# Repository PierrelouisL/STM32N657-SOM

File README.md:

The SOM is not finished yet, still in design.

Should be printed & assembled by November 2026.

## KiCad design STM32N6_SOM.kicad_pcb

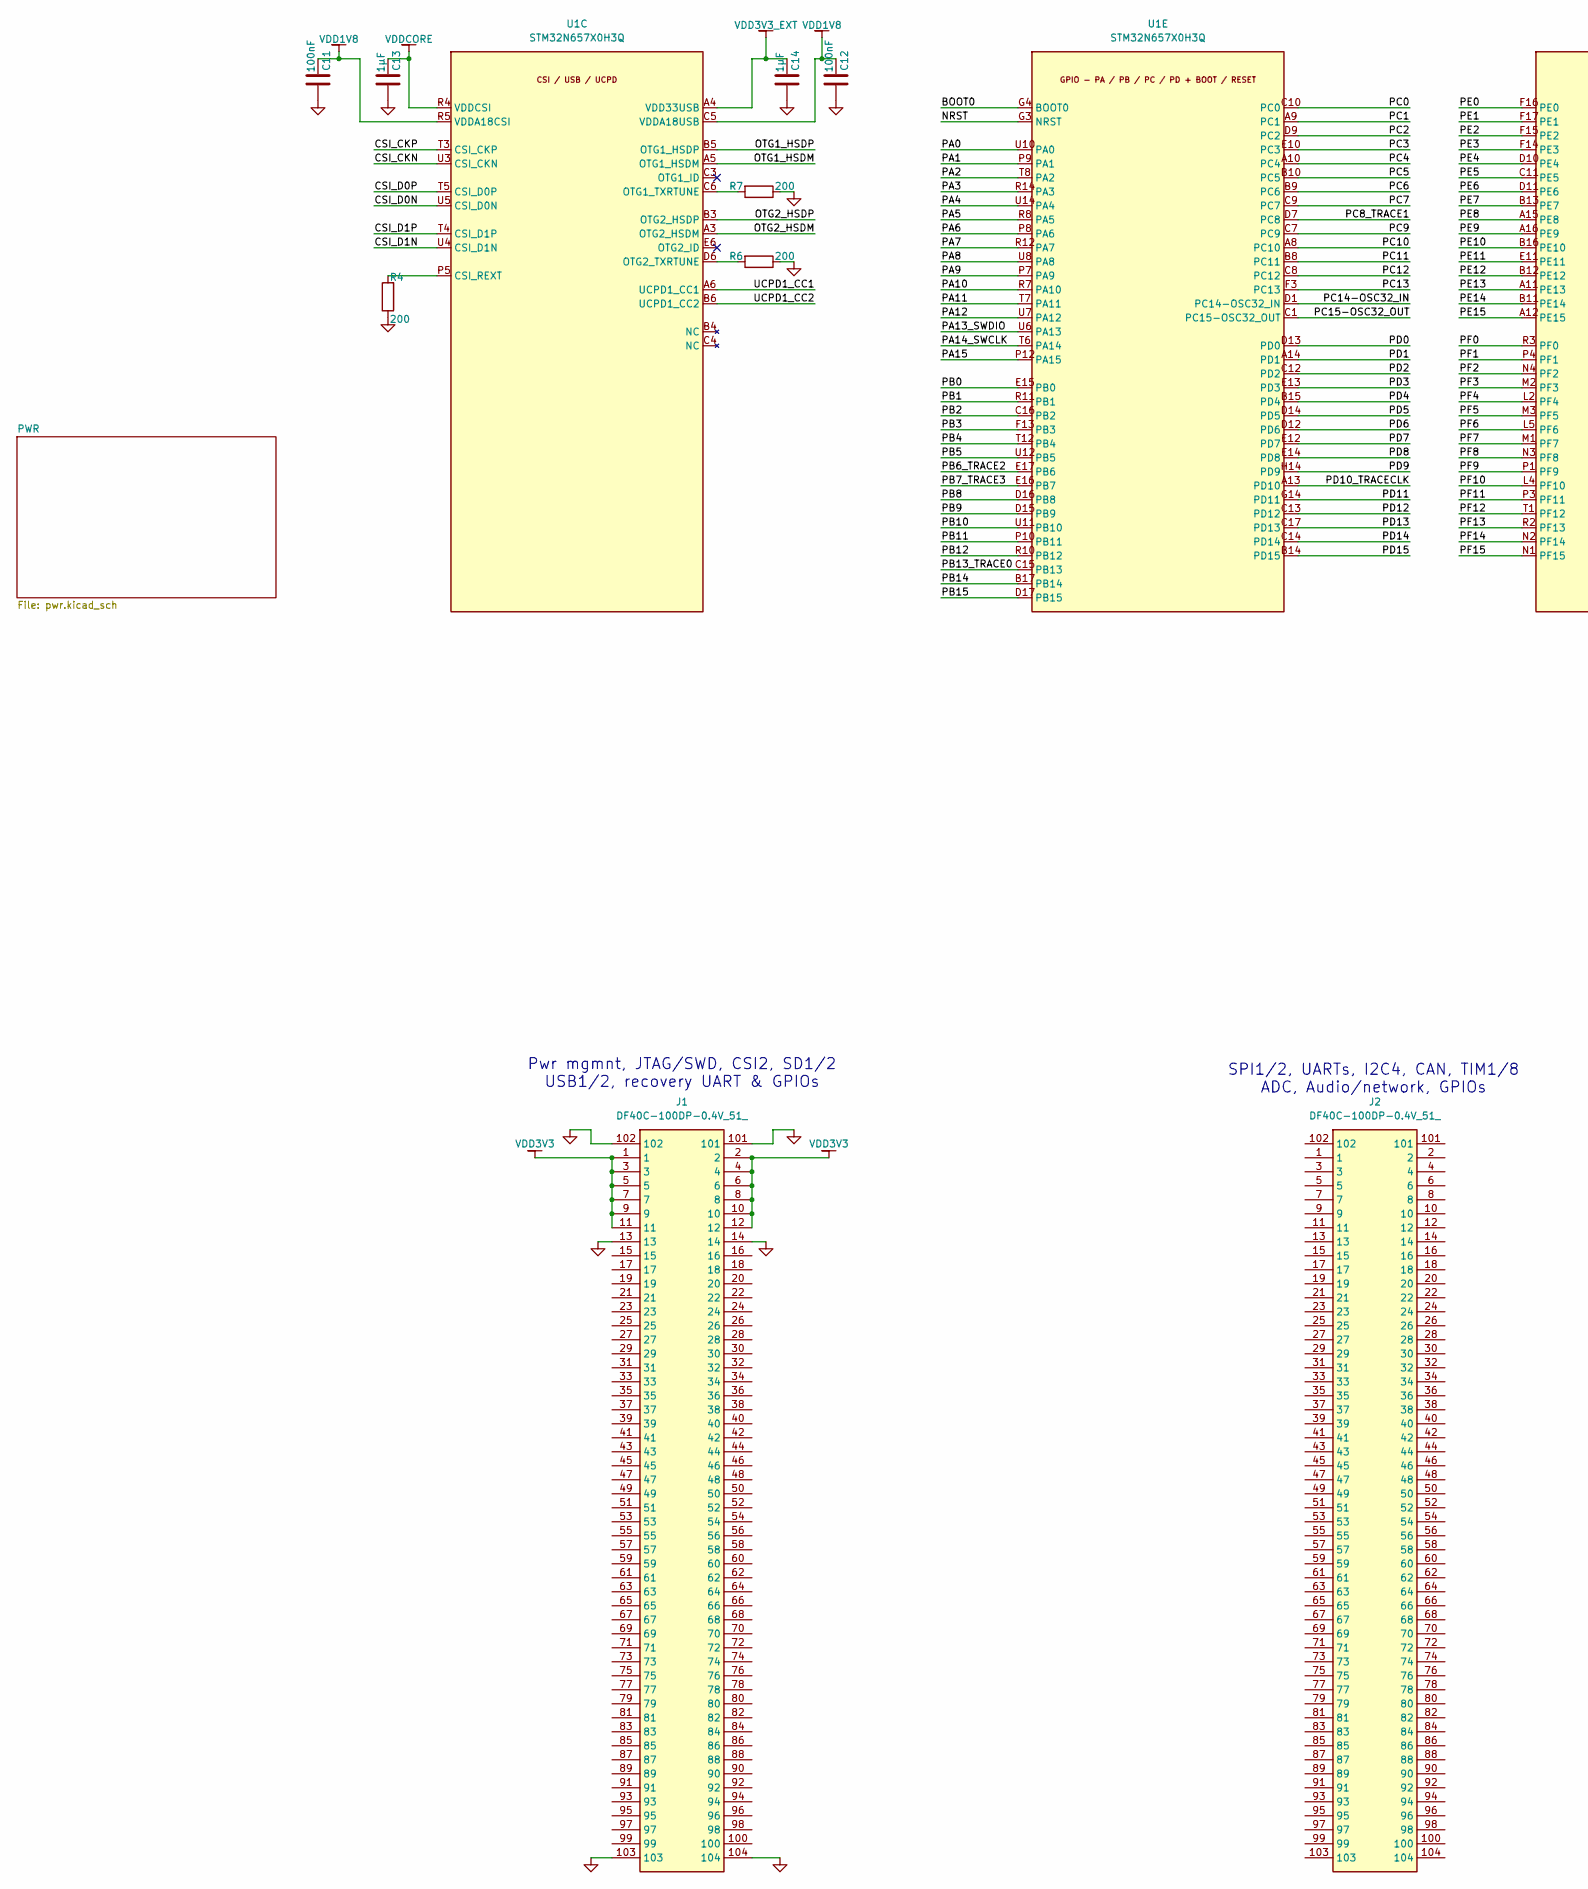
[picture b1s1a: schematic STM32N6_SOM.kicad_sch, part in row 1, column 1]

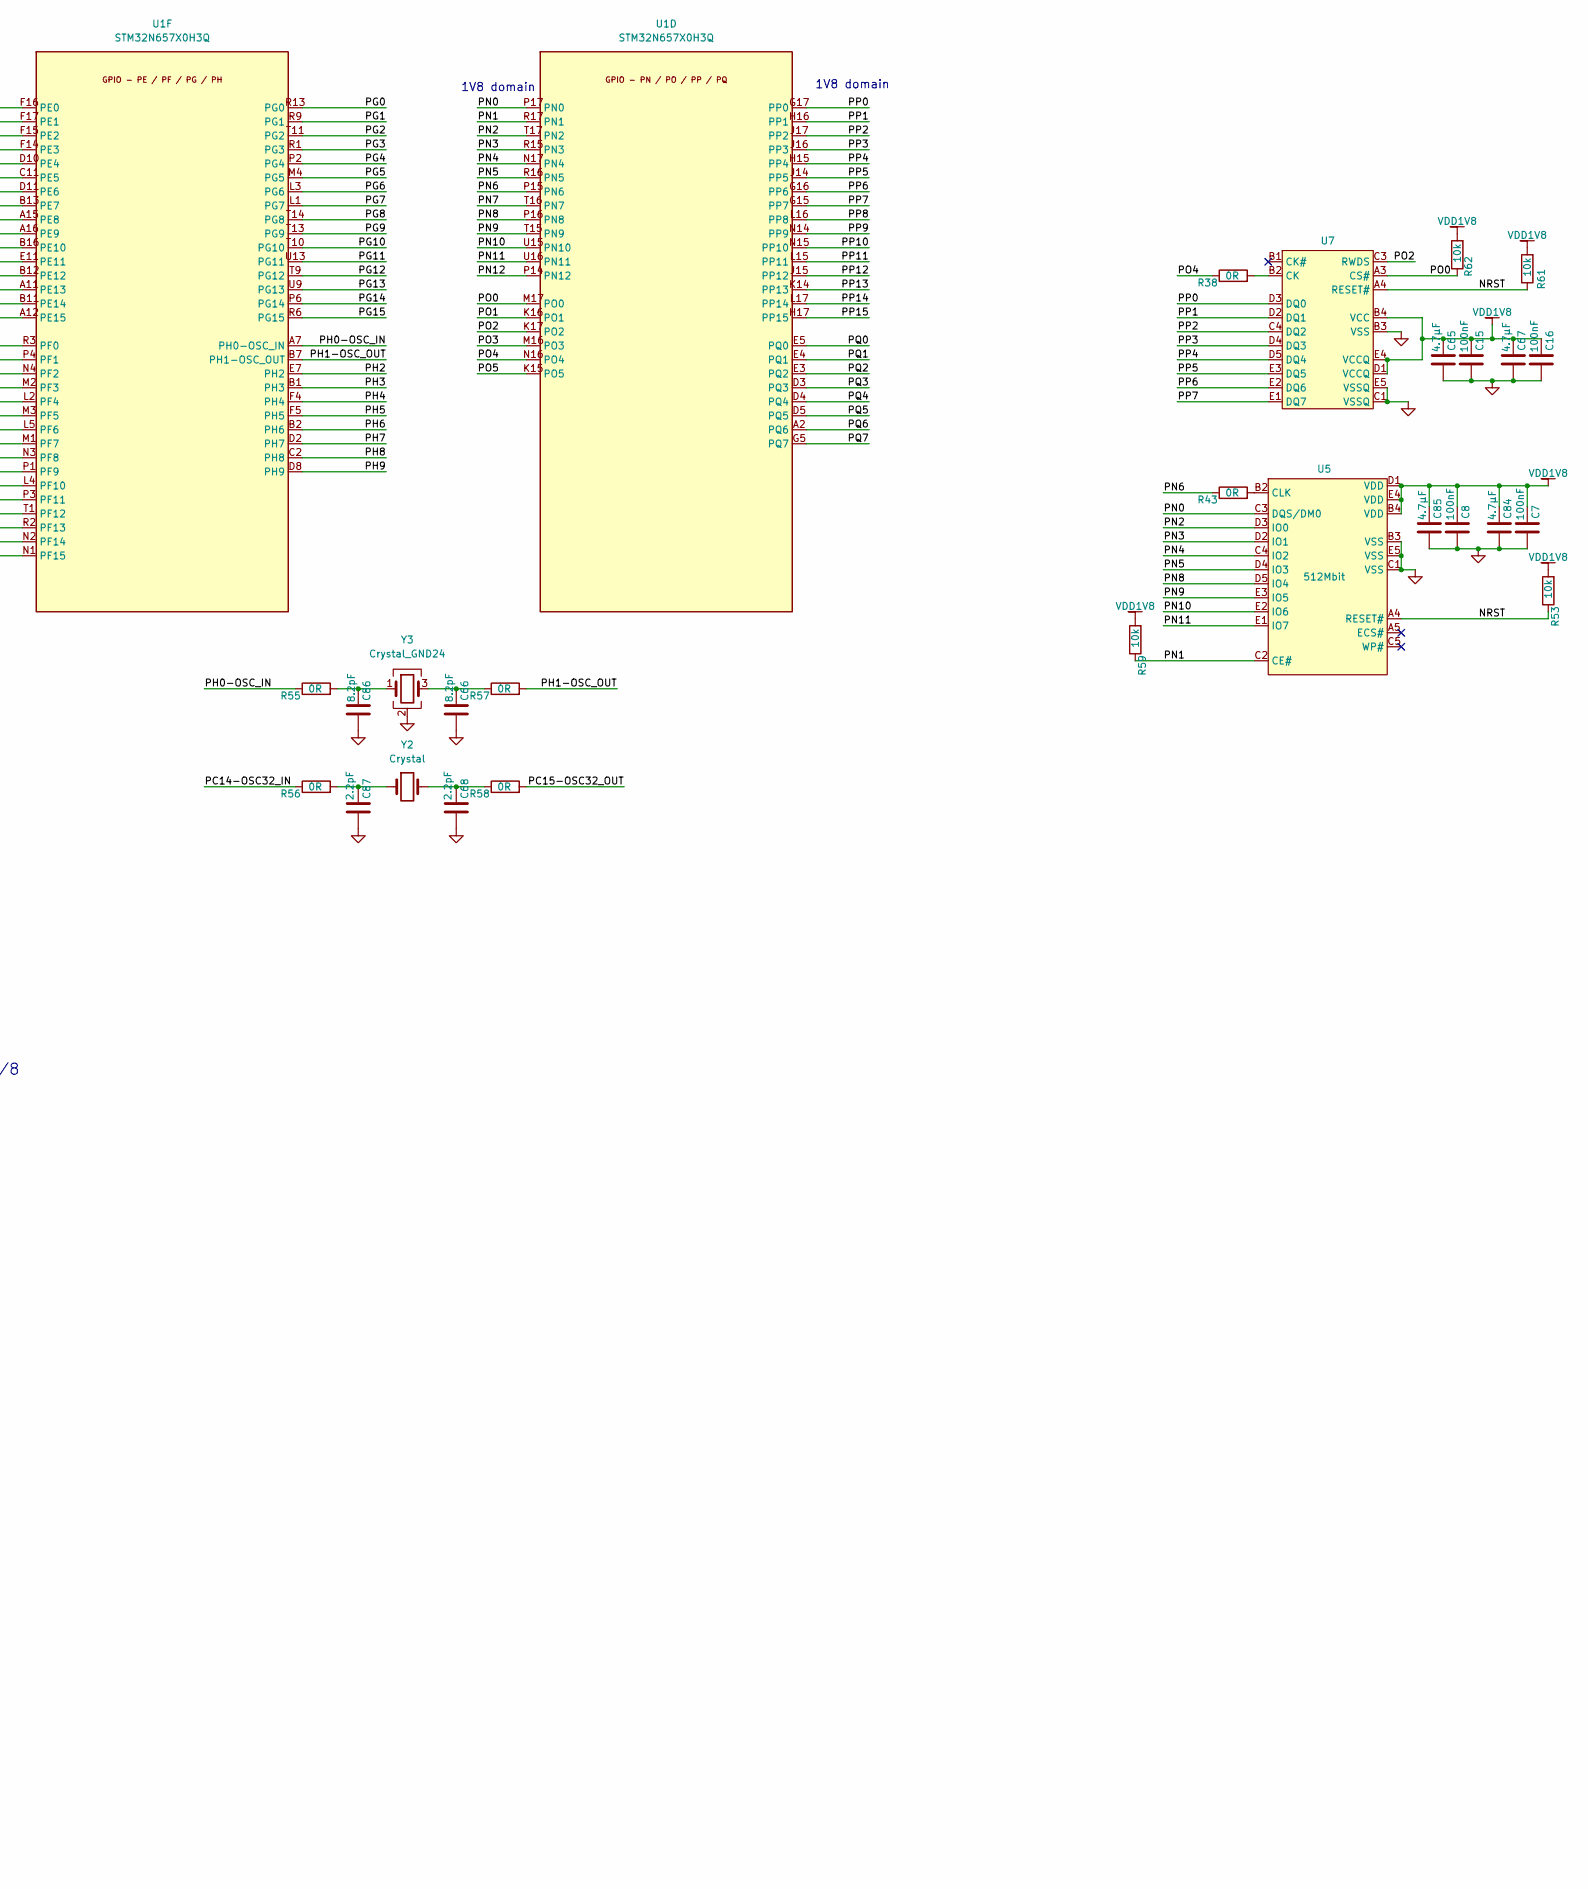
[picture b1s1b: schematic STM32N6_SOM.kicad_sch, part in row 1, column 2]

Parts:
C7, C8, C11, C12, C15, C16: 100nF; C_0201_0603Metric
C13, C14: 1µF; C_0201_0603Metric
C65, C67, C84, C85: 4.7µF; C_0402_1005Metric
C66, C86: 8.2pF; C_0402_1005Metric
C68, C87: 2.2pF; C_0402_1005Metric
J1, J2: DF40C-100DP-0.4V_51_; DF40C100DP04V51; Manufacturer_Part_Number DF40C-100DP-0.4V(51); Mouser Part Number 798-DF40C100DP0.4V51
R4, R6, R7: 200; R_0402_1005Metric
R38, R43, R55, R56, R57, R58: 0R; C_0402_1005Metric
R53, R59, R61, R62: 10k; C_0402_1005Metric
U1: STM32N657X0H3Q; BGA264C80P17X17_1400X1400X100; MPN STM32N657X0H3Q; LCSC Part C42418080
U5: 512Mbit; tfbga24 (6_8mm2); LCSC C20099949
U7: tfbga24 (6_8mm2); LCSC C7420405
Y2: Crystal; C1987116; LCSC C1987116
Y3: Crystal_GND24; C1985871; LCSC C1985871

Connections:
/BOOT0: U1.G4 (BOOT0)
/CSI_CKN: U1.U3 (CSI_CKN)
/CSI_CKP: U1.T3 (CSI_CKP)
/CSI_D0N: U1.U5 (CSI_D0N)
/CSI_D0P: U1.T5 (CSI_D0P)
/CSI_D1N: U1.U4 (CSI_D1N)
/CSI_D1P: U1.T4 (CSI_D1P)
/NRST: R53.1, R61.1, U1.G3 (NRST), U5.A4 (RESET#), U7.A4 (RESET#)
/OTG1_HSDM: U1.A5 (OTG1_HSDM)
/OTG1_HSDP: U1.B5 (OTG1_HSDP)
/OTG2_HSDM: U1.A3 (OTG2_HSDM)
/OTG2_HSDP: U1.B3 (OTG2_HSDP)
/PA0: U1.U10 (PA0)
/PA1: U1.P9 (PA1)
/PA2: U1.T8 (PA2)
/PA3: U1.R14 (PA3)
/PA4: U1.U14 (PA4)
/PA5: U1.R8 (PA5)
/PA6: U1.P8 (PA6)
/PA7: U1.R12 (PA7)
/PA8: U1.U8 (PA8)
/PA9: U1.P7 (PA9)
/PA10: U1.R7 (PA10)
/PA11: U1.T7 (PA11)
/PA12: U1.U7 (PA12)
/PA13_SWDIO: U1.U6 (PA13)
/PA14_SWCLK: U1.T6 (PA14)
/PA15: U1.P12 (PA15)
/PB0: U1.E15 (PB0)
/PB1: U1.R11 (PB1)
/PB2: U1.C16 (PB2)
/PB3: U1.F13 (PB3)
/PB4: U1.T12 (PB4)
/PB5: U1.U12 (PB5)
/PB6_TRACE2: U1.E17 (PB6)
/PB7_TRACE3: U1.E16 (PB7)
/PB8: U1.D16 (PB8)
/PB9: U1.D15 (PB9)
/PB10: U1.U11 (PB10)
/PB11: U1.P10 (PB11)
/PB12: U1.R10 (PB12)
/PB13_TRACE0: U1.C15 (PB13)
/PB14: U1.B17 (PB14)
/PB15: U1.D17 (PB15)
/PC0: U1.C10 (PC0)
/PC1: U1.A9 (PC1)
/PC2: U1.D9 (PC2)
/PC3: U1.E10 (PC3)
/PC4: U1.A10 (PC4)
/PC5: U1.B10 (PC5)
/PC6: U1.B9 (PC6)
/PC7: U1.C9 (PC7)
/PC8_TRACE1: U1.D7 (PC8)
/PC9: U1.C7 (PC9)
/PC10: U1.A8 (PC10)
/PC11: U1.B8 (PC11)
/PC12: U1.C8 (PC12)
/PC13: U1.F3 (PC13)
/PC14-OSC32_IN: R56.1, U1.D1 (PC14-OSC32_IN)
/PC15-OSC32_OUT: R58.2, U1.C1 (PC15-OSC32_OUT)
/PD0: U1.D13 (PD0)
/PD1: U1.A14 (PD1)
/PD2: U1.C12 (PD2)
/PD3: U1.E13 (PD3)
/PD4: U1.B15 (PD4)
/PD5: U1.D14 (PD5)
/PD6: U1.D12 (PD6)
/PD7: U1.E12 (PD7)
/PD8: U1.E14 (PD8)
/PD9: U1.H14 (PD9)
/PD10_TRACECLK: U1.A13 (PD10)
/PD11: U1.G14 (PD11)
/PD12: U1.C13 (PD12)
/PD13: U1.C17 (PD13)
/PD14: U1.C14 (PD14)
/PD15: U1.B14 (PD15)
/PE0: U1.F16 (PE0)
/PE1: U1.F17 (PE1)
/PE2: U1.F15 (PE2)
/PE3: U1.F14 (PE3)
/PE4: U1.D10 (PE4)
/PE5: U1.C11 (PE5)
/PE6: U1.D11 (PE6)
/PE7: U1.B13 (PE7)
/PE8: U1.A15 (PE8)
/PE9: U1.A16 (PE9)
/PE10: U1.B16 (PE10)
/PE11: U1.E11
/PE12: U1.B12 (PE12)
/PE13: U1.A11 (PE13)
/PE14: U1.B11 (PE14)
/PE15: U1.A12 (PE15)
/PF0: U1.R3 (PF0)
/PF1: U1.P4 (PF1)
/PF2: U1.N4 (PF2)
/PF3: U1.M2 (PF3)
/PF4: U1.L2 (PF4)
/PF5: U1.M3 (PF5)
/PF6: U1.L5 (PF6)
/PF7: U1.M1 (PF7)
/PF8: U1.N3 (PF8)
/PF9: U1.P1 (PF9)
/PF10: U1.L4 (PF10)
/PF11: U1.P3 (PF11)
/PF12: U1.T1 (PF12)
/PF13: U1.R2 (PF13)
/PF14: U1.N2 (PF14)
/PF15: U1.N1 (PF15)
/PG0: U1.R13 (PG0)
/PG1: U1.R9 (PG1)
/PG2: U1.T11 (PG2)
/PG3: U1.R1 (PG3)
/PG4: U1.P2 (PG4)
/PG5: U1.M4 (PG5)
/PG6: U1.L3 (PG6)
/PG7: U1.L1 (PG7)
/PG8: U1.T14 (PG8)
/PG9: U1.T13 (PG9)
/PG10: U1.T10 (PG10)
/PG11: U1.U13 (PG11)
/PG12: U1.T9 (PG12)
/PG13: U1.U9 (PG13)
/PG14: U1.P6 (PG14)
/PG15: U1.R6 (PG15)
/PH0-OSC_IN: R55.1, U1.A7 (PH0-OSC_IN)
/PH1-OSC_OUT: R57.2, U1.B7 (PH1-OSC_OUT)
/PH2: U1.E7 (PH2)
/PH3: U1.B1 (PH3)
/PH4: U1.F4 (PH4)
/PH5: U1.F5 (PH5)
/PH6: U1.B2 (PH6)
/PH7: U1.D2 (PH7)
/PH8: U1.C2 (PH8)
/PH9: U1.D8 (PH9)
/PN0: U1.P17 (PN0), U5.C3 (DQS/DM0)
/PN1: R59.1, U1.R17 (PN1), U5.C2 (CE#)
/PN2: U1.T17 (PN2), U5.D3 (IO0)
/PN3: U1.R15 (PN3), U5.D2 (IO1)
/PN4: U1.N17 (PN4), U5.C4 (IO2)
/PN5: U1.R16 (PN5), U5.D4 (IO3)
/PN6: R43.1, U1.P15 (PN6)
/PN7: U1.T16 (PN7)
/PN8: U1.P16 (PN8), U5.D5 (IO4)
/PN9: U1.T15 (PN9), U5.E3 (IO5)
/PN10: U1.U15 (PN10), U5.E2 (IO6)
/PN11: U1.U16 (PN11), U5.E1 (IO7)
/PN12: U1.P14 (PN12)
/PO0: R62.1, U1.M17 (PO0), U7.A3 (CS#)
/PO1: U1.K16 (PO1)
/PO2: U1.K17 (PO2), U7.C3 (RWDS)
/PO3: U1.M16 (PO3)
/PO4: R38.1, U1.N16 (PO4)
/PO5: U1.K15 (PO5)
/PP0: U1.G17 (PP0), U7.D3 (DQ0)
/PP1: U1.H16 (PP1), U7.D2 (DQ1)
/PP2: U1.J17 (PP2), U7.C4 (DQ2)
/PP3: U1.J16 (PP3), U7.D4 (DQ3)
/PP4: U1.H15 (PP4), U7.D5 (DQ4)
/PP5: U1.J14 (PP5), U7.E3 (DQ5)
/PP6: U1.G16 (PP6), U7.E2 (DQ6)
/PP7: U1.G15 (PP7), U7.E1 (DQ7)
/PP8: U1.L16 (PP8)
/PP9: U1.N14 (PP9)
/PP10: U1.N15 (PP10)
/PP11: U1.L15 (PP11)
/PP12: U1.J15 (PP12)
/PP13: U1.K14 (PP13)
/PP14: U1.L17 (PP14)
/PP15: U1.H17 (PP15)
/PQ0: U1.E5 (PQ0)
/PQ1: U1.E4 (PQ1)
/PQ2: U1.E3 (PQ2)
/PQ3: U1.D3 (PQ3)
/PQ4: U1.D4 (PQ4)
/PQ5: U1.D5 (PQ5)
/PQ6: U1.A2 (PQ6)
/PQ7: U1.G5 (PQ7)
/UCPD1_CC1: U1.A6 (UCPD1_CC1)
/UCPD1_CC2: U1.B6 (UCPD1_CC2)
GND: C7.2, C8.2, C11.2, C12.2, C13.2, C14.2, C15.2, C16.2, C65.2, C66.2, C67.2, C68.2, C84.2, C85.2, C86.2, C87.2, J1.13, J1.14, J1.101, J1.102, J1.103, J1.104, R4.1, R6.1, R7.1, U5.B3 (VSS), U5.C1 (VSS), U5.E5 (VSS), U7.B3 (VSS), U7.C1 (VSSQ), U7.E5 (VSSQ), Y3.2 (G), Y3.4 (G); also elsewhere on the board
unnamed: C66.1, R57.1, Y3.3
unnamed: C68.1, R58.1, Y2.2
unnamed: C86.1, R55.2, Y3.1
unnamed: C87.1, R56.2, Y2.1
unnamed: R4.2, U1.P5 (CSI_REXT)
unnamed: R7.2, U1.C6 (OTG1_TXRTUNE)
unnamed: R6.2, U1.D6 (OTG2_TXRTUNE)
unnamed: R43.2, U5.B2 (CLK)
unnamed: U5.A2 (NC), U5.A3 (NC), U5.B1 (NC), U5.B5 (NC)
unnamed: R38.2, U7.B2 (CK)
VDD1V8: C7.1, C8.1, C11.1, C12.1, C15.1, C16.1, C65.1, C67.1, C84.1, C85.1, R53.2, R59.2, R61.2, R62.2, U1.C5 (VDDA18USB), U1.R5 (VDDA18CSI), U5.B4 (VDD), U5.D1 (VDD), U5.E4 (VDD), U7.B4 (VCC), U7.D1 (VCCQ), U7.E4 (VCCQ); also elsewhere on the board
VDD3V3: J1.1, J1.2, J1.3, J1.4, J1.5, J1.6, J1.7, J1.8, J1.9, J1.10, J1.11, J1.12; also elsewhere on the board
VDD3V3_EXT: C14.1, U1.A4 (VDD33USB); also elsewhere on the board
VDDCORE: C13.1, U1.R4 (VDDCSI); also elsewhere on the board

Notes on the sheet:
1V8 domain
Pwr mgmnt, JTAG/SWD, CSI2, SD1/2 USB1/2, recovery UART & GPIOs
SPI1/2, UARTs, I2C4, CAN, TIM1/8 ADC, Audio/network, GPIOs

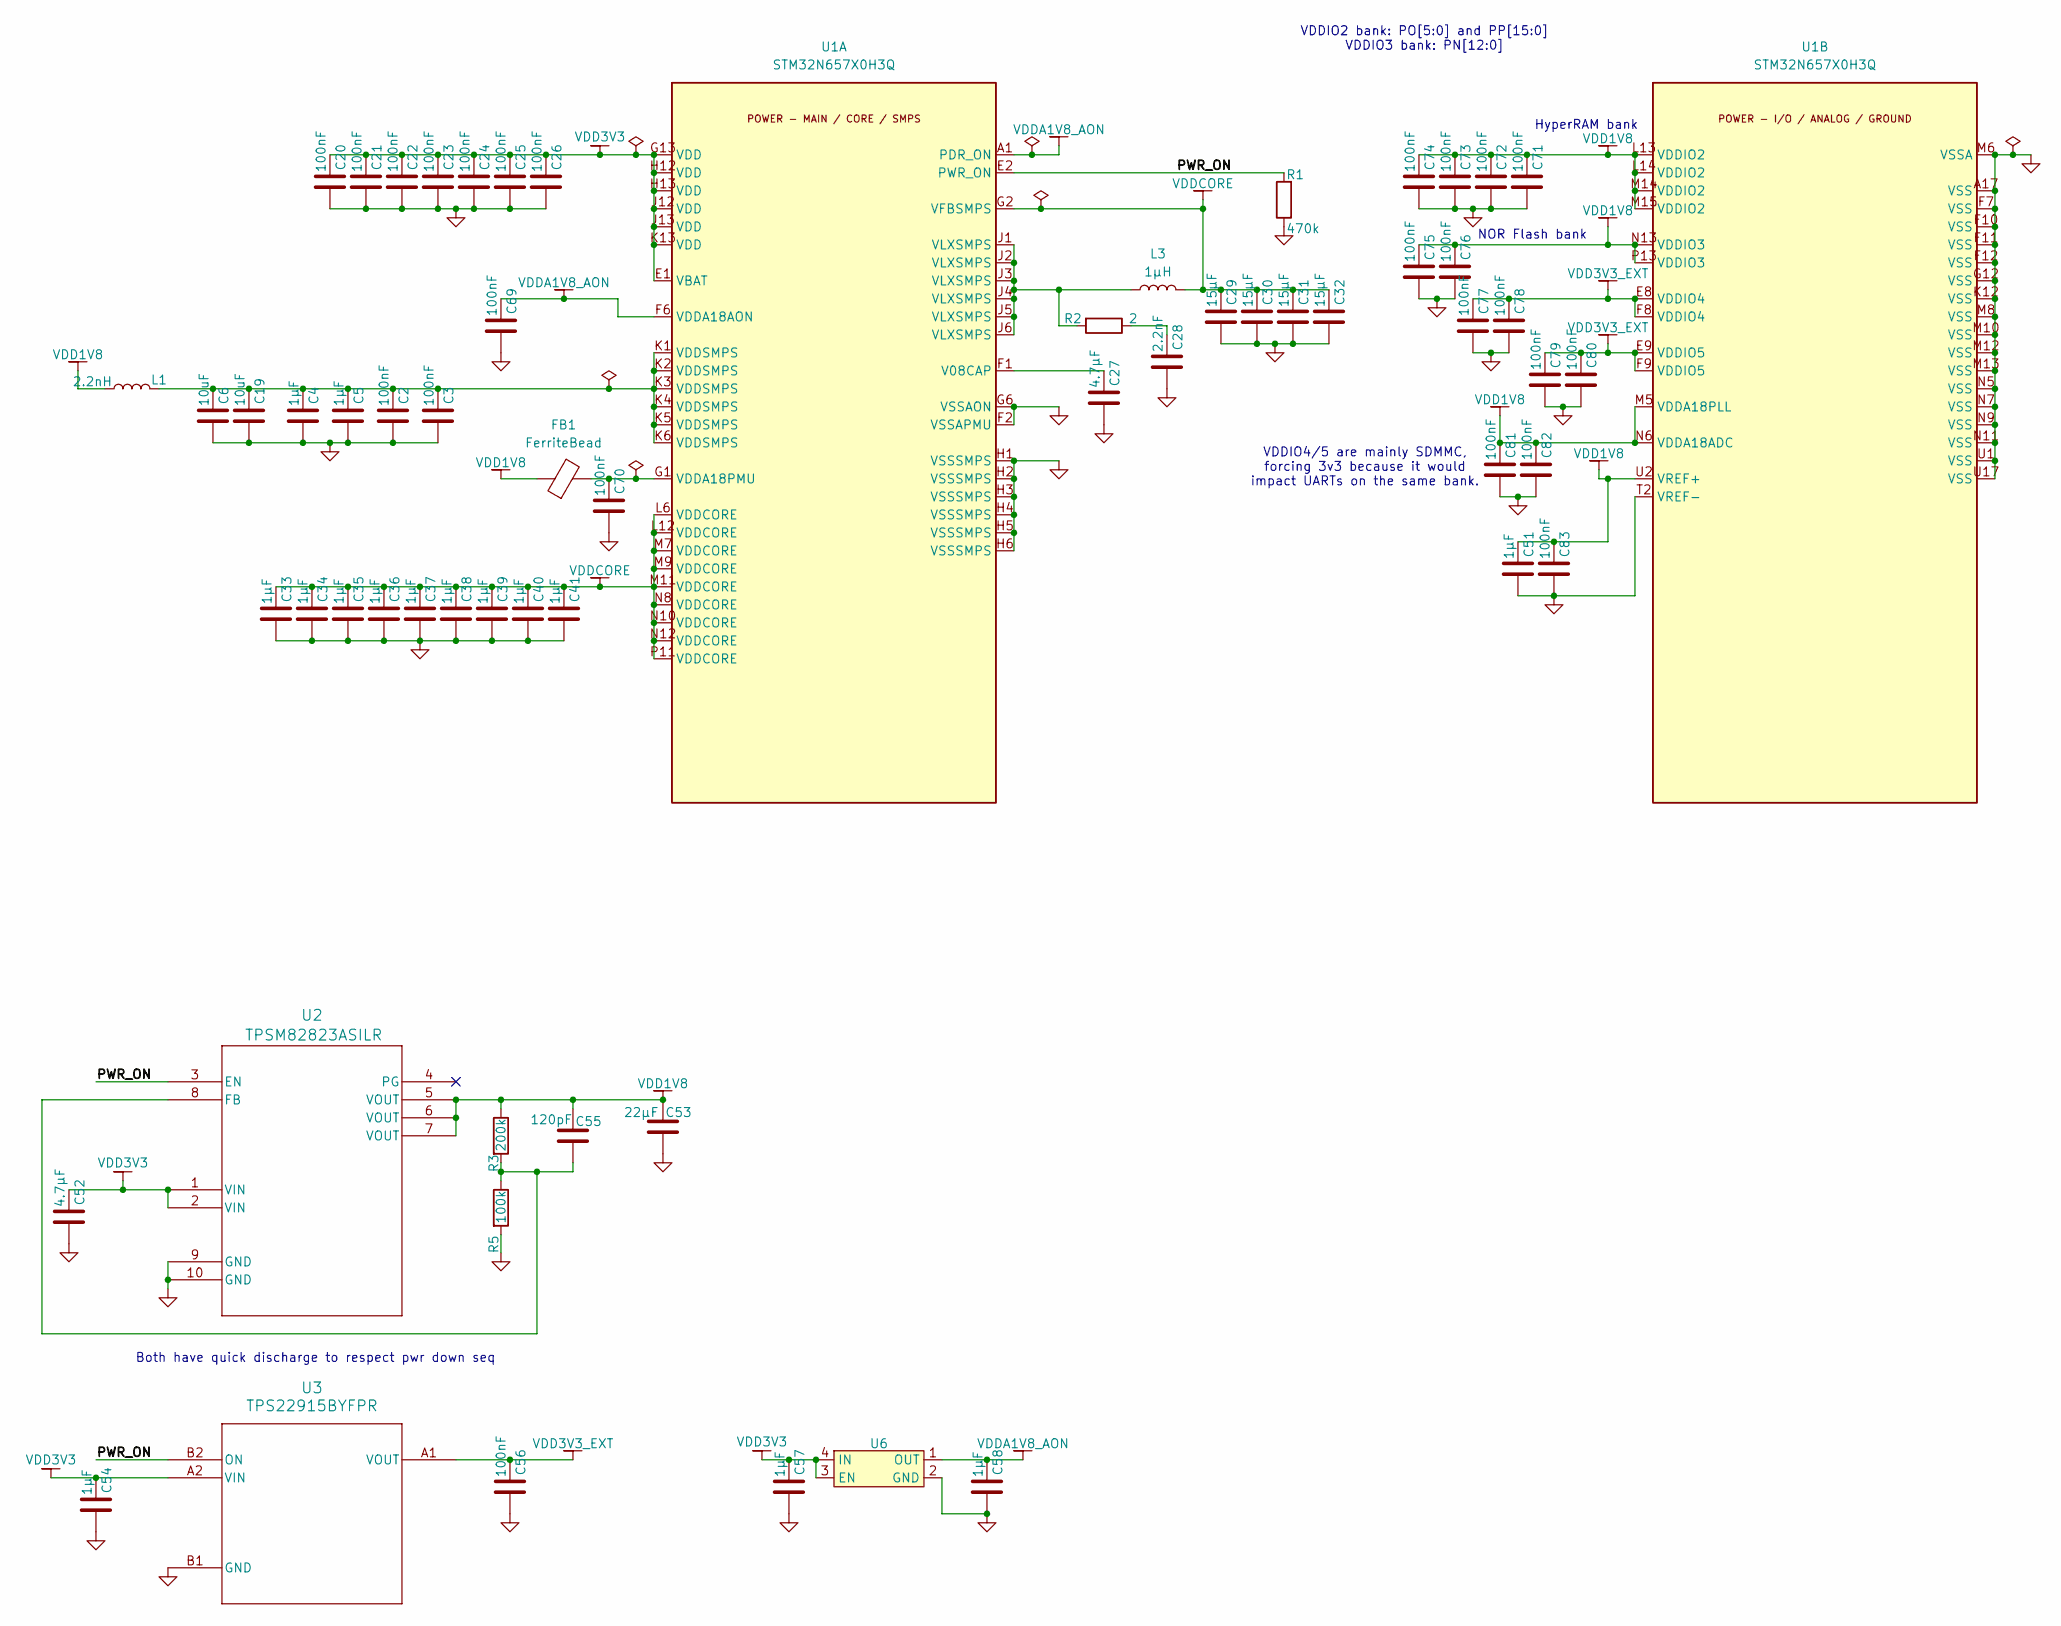
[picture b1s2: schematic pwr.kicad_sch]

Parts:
C2, C3, C20, C21, C22, C23, C24, C25, C26, C69, C70, C71, C72, C73, C74, C75, C76, C77, C78, C79, C80, C81, C82, C83: 100nF; C_0201_0603Metric
C4, C5, C33, C34, C35, C36, C37, C38, C39, C40, C41, C51: 1µF; C_0201_0603Metric
C6, C19: 10uF; C_0402_1005Metric
C27: 4.7µF; C_0402_1005Metric
C28: 2.2nF; C_0402_1005Metric
C29, C30, C31, C32: 15µF; C_0603_1608Metric
C52: 4.7µF; C_0603_1608Metric
C53: 22µF; C_0603_1608Metric
C54, C57, C58: 1µF; C_0402_1005Metric
C55: 120pF; C_0603_1608Metric
C56: 100nF; C_0402_1005Metric
FB1: FerriteBead; L_0201_0603Metric; LCSC C3032750
L1: 2.2nH; C_0603_1608Metric
L3: 1µH; C_0805_2012Metric; LCSC C1042
R1: 470k; R_0402_1005Metric; LCSC C25790
R2: 2; R_0402_1005Metric
R3: 200k; R_0402_1005Metric
R5: 100k; R_0402_1005Metric
U1: STM32N657X0H3Q; BGA264C80P17X17_1400X1400X100; MPN STM32N657X0H3Q; LCSC Part C42418080
U2: TPSM82823ASILR; SIL0010D_TEX; LCSC C5219332
U3: TPS22915BYFPR; YFP4_TEX; LCSC C478464
U6: DQN_X2SON4_1mmx1mm; LCSC C3744287

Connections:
/PWR/PWR_ON: R1.2, U1.E2 (PWR_ON), U2.3 (EN), U3.B2 (ON)
GND: C2.2, C3.2, C4.2, C5.2, C6.2, C19.2, C20.2, C21.2, C22.2, C23.2, C24.2, C25.2, C26.2, C27.2, C28.2, C29.2, C30.2, C31.2, C32.2, C33.2, C34.2, C35.2, C36.2, C37.2, C38.2, C39.2, C40.2, C41.2, C51.2, C52.2, C53.2, C54.2, C56.2, C57.2, C58.2, C69.2, C70.2, C71.2, C72.2, C73.2, C74.2, C75.2, C76.2, C77.2, C78.2, C79.2, C80.2, C81.2, C82.2, C83.2, R1.1, R5.2, U1.A17 (VSS), U1.F2 (VSSAPMU), U1.F7 (VSS), U1.F10 (VSS), U1.F11 (VSS), U1.F12 (VSS), U1.G6 (VSSAON), U1.G12 (VSS), U1.H1 (VSSSMPS), U1.H2 (VSSSMPS), U1.H3 (VSSSMPS), U1.H4 (VSSSMPS), U1.H5 (VSSSMPS), U1.H6 (VSSSMPS), U1.K12 (VSS), U1.M6 (VSSA), U1.M8 (VSS), U1.M10 (VSS), U1.M12 (VSS), U1.M13 (VSS), U1.N5 (VSS), U1.N7 (VSS), U1.N9 (VSS), U1.N11 (VSS), U1.T2 (VREF-), U1.U1 (VSS), U1.U17 (VSS), U2.9 (GND), U2.10 (GND), U3.B1 (GND), U6.2 (GND), U6.5 (THERM); also elsewhere on the board
unnamed: C2.1, C3.1, C4.1, C5.1, C6.1, C19.1, L1.1, U1.K1 (VDDSMPS), U1.K2 (VDDSMPS), U1.K3 (VDDSMPS), U1.K4 (VDDSMPS), U1.K5 (VDDSMPS), U1.K6 (VDDSMPS)
unnamed: C28.1, R2.1
unnamed: L3.2, R2.2, U1.J1 (VLXSMPS), U1.J2 (VLXSMPS), U1.J3 (VLXSMPS), U1.J4 (VLXSMPS), U1.J5 (VLXSMPS), U1.J6 (VLXSMPS)
unnamed: C27.1, U1.F1 (V08CAP)
unnamed: C70.1, FB1.2, U1.G1 (VDDA18PMU)
unnamed: C55.2, R3.2, R5.1, U2.8 (FB)
VDD1V8: C51.1, C53.1, C55.1, C71.1, C72.1, C73.1, C74.1, C75.1, C76.1, C81.1, C82.1, C83.1, FB1.1, L1.2, R3.1, U1.L13 (VDDIO2), U1.L14 (VDDIO2), U1.M5 (VDDA18PLL), U1.M14 (VDDIO2), U1.M15 (VDDIO2), U1.N6 (VDDA18ADC), U1.N13 (VDDIO3), U1.P13 (VDDIO3), U1.U2 (VREF+), U2.5 (VOUT), U2.6 (VOUT), U2.7 (VOUT); also elsewhere on the board
VDD3V3: C20.1, C21.1, C22.1, C23.1, C24.1, C25.1, C26.1, C52.1, C54.1, C57.1, U1.E1 (VBAT), U1.G13 (VDD), U1.H12 (VDD), U1.H13 (VDD), U1.J12 (VDD), U1.J13 (VDD), U1.K13 (VDD), U2.1 (VIN), U2.2 (VIN), U3.A2 (VIN), U6.3 (EN), U6.4 (IN); also elsewhere on the board
VDD3V3_EXT: C56.1, C77.1, C78.1, C79.1, C80.1, U1.E8 (VDDIO4), U1.E9 (VDDIO5), U1.F8 (VDDIO4), U1.F9 (VDDIO5), U3.A1 (VOUT); also elsewhere on the board
VDDA1V8_AON: C58.1, C69.1, U1.A1 (PDR_ON), U1.F6 (VDDA18AON), U6.1 (OUT)
VDDCORE: C29.1, C30.1, C31.1, C32.1, C33.1, C34.1, C35.1, C36.1, C37.1, C38.1, C39.1, C40.1, C41.1, L3.1, U1.G2 (VFBSMPS), U1.L6 (VDDCORE), U1.L12 (VDDCORE), U1.M7 (VDDCORE), U1.M9 (VDDCORE), U1.M11 (VDDCORE), U1.N8 (VDDCORE), U1.N10 (VDDCORE), U1.N12 (VDDCORE), U1.P11 (VDDCORE); also elsewhere on the board

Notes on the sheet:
VDDIO2 bank: PO[5:0] and PP[15:0] VDDIO3 bank: PN[12:0]
Both have quick discharge to respect pwr down seq
VDDIO4/5 are mainly SDMMC, forcing 3v3 because it would impact UARTs on the same bank.
HyperRAM bank
NOR Flash bank

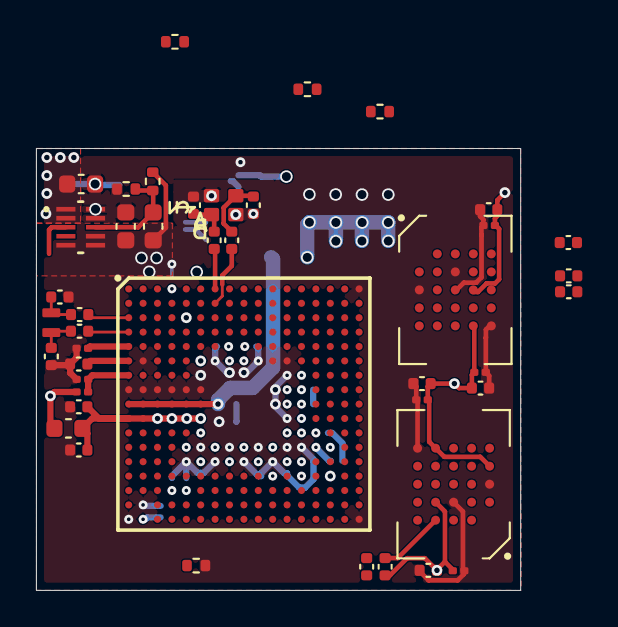
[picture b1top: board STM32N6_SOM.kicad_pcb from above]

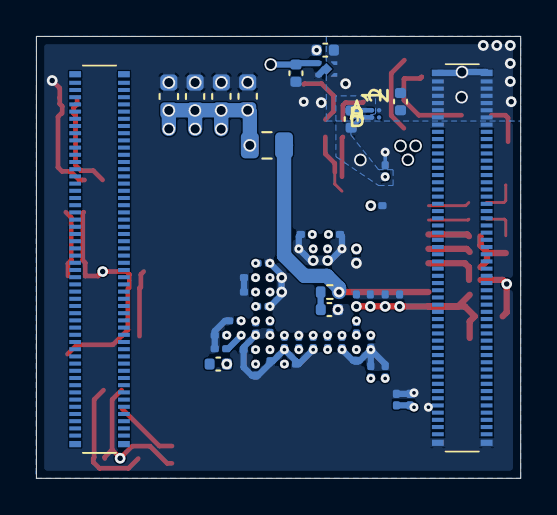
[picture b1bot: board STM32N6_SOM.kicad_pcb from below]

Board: 8 copper layers, 26.9 x 24.5 mm, 97 parts (54 on the bottom side), 50 nets.

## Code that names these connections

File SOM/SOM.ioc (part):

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Mcu.Name=STM32N657X0HxQ
Mcu.Package=VFBGA264
Mcu.UserName=STM32N657X0HxQ
PA13(JTMS/SWDIO).GPIOParameters=PinAttribute
PA13(JTMS/SWDIO).Mode=Trace_Synchro_4bits_JTAG
PA13(JTMS/SWDIO).PinAttribute=AppliNonSecure
PA13(JTMS/SWDIO).Signal=DEBUG_JTMS-SWDIO
PA14(JTCK/SWCLK).GPIOParameters=PinAttribute
PA14(JTCK/SWCLK).Mode=Trace_Synchro_4bits_JTAG
PA14(JTCK/SWCLK).PinAttribute=AppliNonSecure
PA14(JTCK/SWCLK).Signal=DEBUG_JTCK-SWCLK
PA15(JTDI).GPIOParameters=PinAttribute
PA15(JTDI).Mode=Trace_Synchro_4bits_JTAG
PA15(JTDI).PinAttribute=AppliNonSecure
PA15(JTDI).Signal=DEBUG_JTDI
PA6.Signal=BOOT1
PB13.GPIOParameters=PinAttribute
PB13.Mode=Trace_Synchro_4bits_JTAG
PB13.PinAttribute=AppliNonSecure
PB13.Signal=DEBUG_TRACED0
PB2.GPIOParameters=PinAttribute
PB2.Mode=External_Trigger_Input
PB2.PinAttribute=FSBL,AppliNonSecure
PB2.Signal=HDP_HDP2
PB5(JTDO/TRACESWO).GPIOParameters=PinAttribute
PB5(JTDO/TRACESWO).Mode=Trace_Synchro_4bits_JTAG
PB5(JTDO/TRACESWO).PinAttribute=AppliNonSecure
PB5(JTDO/TRACESWO).Signal=DEBUG_JTDO-SWO
PB6.GPIOParameters=PinAttribute
PB6.Mode=Trace_Synchro_4bits_JTAG
PB6.PinAttribute=AppliNonSecure
PB6.Signal=DEBUG_TRACED2
PB7.GPIOParameters=PinAttribute
PB7.Mode=Trace_Synchro_4bits_JTAG
PB7.PinAttribute=AppliNonSecure
PB7.Signal=DEBUG_TRACED3
PC0.GPIOParameters=PinAttribute
PC0.Mode=sdio_4_bits_Wide_bus
PC0.PinAttribute=AppliNonSecure
PC0.Signal=SDMMC2_D2
PC1.GPIOParameters=PinAttribute
PC1.Mode=External_Trigger_Input
PC1.PinAttribute=FSBL,AppliNonSecure
PC1.Signal=HDP_HDP1
PC10.GPIOParameters=PinAttribute
PC10.Mode=SD_4_bits_Wide_bus
PC10.PinAttribute=AppliNonSecure
PC10.Signal=SDMMC1_D2
PC11.GPIOParameters=PinAttribute
PC11.Mode=SD_4_bits_Wide_bus
PC11.PinAttribute=AppliNonSecure
PC11.Signal=SDMMC1_D3
PC12.GPIOParameters=PinAttribute
PC12.Mode=SD_4_bits_Wide_bus
PC12.PinAttribute=AppliNonSecure
PC12.Signal=SDMMC1_CK
PC14-OSC32_IN(OSC32_IN).GPIOParameters=PinAttribute
PC14-OSC32_IN(OSC32_IN).Mode=LSE-External-Oscillator
PC14-OSC32_IN(OSC32_IN).PinAttribute=Free
PC14-OSC32_IN(OSC32_IN).Signal=RCC_OSC32_IN
PC15-OSC32_OUT(OSC32_OUT).GPIOParameters=PinAttribute
PC15-OSC32_OUT(OSC32_OUT).Mode=LSE-External-Oscillator
PC15-OSC32_OUT(OSC32_OUT).PinAttribute=Free
PC15-OSC32_OUT(OSC32_OUT).Signal=RCC_OSC32_OUT
PC3.GPIOParameters=PinAttribute
PC3.Mode=sdio_4_bits_Wide_bus
PC3.PinAttribute=AppliNonSecure
PC3.Signal=SDMMC2_CMD
PC4.GPIOParameters=PinAttribute
PC4.Mode=sdio_4_bits_Wide_bus
PC4.PinAttribute=AppliNonSecure
PC4.Signal=SDMMC2_D0
PC5.GPIOParameters=PinAttribute
PC5.Mode=sdio_4_bits_Wide_bus
PC5.PinAttribute=AppliNonSecure
PC5.Signal=SDMMC2_D1
PC6.GPIOParameters=PinAttribute
PC6.Mode=External_Trigger_Input
PC6.PinAttribute=FSBL,AppliNonSecure
PC6.Signal=HDP_HDP6
PC7.GPIOParameters=PinAttribute
PC7.Mode=External_Trigger_Input
PC7.PinAttribute=FSBL,AppliNonSecure
PC7.Signal=HDP_HDP7
PC8.GPIOParameters=PinAttribute
PC8.Mode=Trace_Synchro_4bits_JTAG
PC8.PinAttribute=AppliNonSecure
PC8.Signal=DEBUG_TRACED1
PC9.GPIOParameters=PinAttribute
PC9.Mode=SD_4_bits_Wide_bus
PC9.PinAttribute=AppliNonSecure
PC9.Signal=SDMMC1_D1
PD10.GPIOParameters=PinAttribute
PD10.Mode=Trace_Synchro_4bits_JTAG
PD10.PinAttribute=AppliNonSecure
PD10.Signal=DEBUG_TRACECLK
PD12.GPIOParameters=PinAttribute
PD12.Mode=External_Trigger_Input
PD12.PinAttribute=FSBL,AppliNonSecure
PD12.Signal=HDP_HDP5
PD2.GPIOParameters=PinAttribute
PD2.Mode=sdio_4_bits_Wide_bus
PD2.PinAttribute=AppliNonSecure
PD2.Signal=SDMMC2_CK
PD7.GPIOParameters=PinAttribute
PD7.Mode=External_Trigger_Input
PD7.PinAttribute=FSBL,AppliNonSecure
PD7.Signal=HDP_HDP3
PE15.GPIOParameters=PinAttribute
PE15.Mode=SD_4_bits_Wide_bus
PE15.PinAttribute=AppliNonSecure
PE15.Signal=SDMMC1_D0
PE4.GPIOParameters=PinAttribute
PE4.Mode=sdio_4_bits_Wide_bus
PE4.PinAttribute=AppliNonSecure
PE4.Signal=SDMMC2_D3
PF4.GPIOParameters=PinAttribute
PF4.Mode=External_Trigger_Input
PF4.PinAttribute=FSBL,AppliNonSecure
PF4.Signal=HDP_HDP4
PH0-OSC_IN(PH0).GPIOParameters=PinAttribute
PH0-OSC_IN(PH0).Mode=HSE-External-Oscillator
PH0-OSC_IN(PH0).PinAttribute=Free
PH0-OSC_IN(PH0).Signal=RCC_OSC_IN
PH1-OSC_OUT(PH1).GPIOParameters=PinAttribute
PH1-OSC_OUT(PH1).Mode=HSE-External-Oscillator
PH1-OSC_OUT(PH1).PinAttribute=Free
PH1-OSC_OUT(PH1).Signal=RCC_OSC_OUT
PH2.GPIOParameters=PinAttribute
PH2.Mode=SD_4_bits_Wide_bus
PH2.PinAttribute=AppliNonSecure
PH2.Signal=SDMMC1_CMD
PH9.GPIOParameters=PinAttribute
PH9.Mode=External_Trigger_Input
PH9.PinAttribute=FSBL,AppliNonSecure
PH9.Signal=HDP_HDP0
RCC.HSE_VALUE=48000000
board=custom
